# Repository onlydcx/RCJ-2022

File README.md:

# このプロジェクトについて
ロボカップジュニア2022に出場する機体の全データです。要はオープンソースです。

需要があるかは分かりませんが、公開すること自体が大事だと思うので公開します

# 3Dデータ
3Dデータ フォルダに入ってます。

Autodesk Fusion360で作成しました、f3zファイルなのでFusionでしか開けないと思います。

# ソフトウェア
PlatfomIOで開発しています。

必要なplatformio.iniとmain.cppだけ載せておきます。

質問とかあったらTwitterでDMしてください

# 基板データ
基板データ フォルダに入ってます。
- 「CamBoard」 メイン基板のデータです。OpenMV,Teensyなどが乗ります
- 「FrontLine」 前のLINEセンサーのデータです。ボール補足エリアがあるので前だけラインセンサの形が違います。
- 「Kicker」 キッカー用のMOSFETが乗った回路です。コンデンサは別付けです。
- 「PowerUnit」 リポから5V,3.3Vを生成してメイン基板に送る回路です。ヒューズも乗ります。
- 「SideLine」 横と後ろのラインセンサーのデータです
- 「UI-unit」 UI基盤のデータです。0.96inchのOLEDが乗ります

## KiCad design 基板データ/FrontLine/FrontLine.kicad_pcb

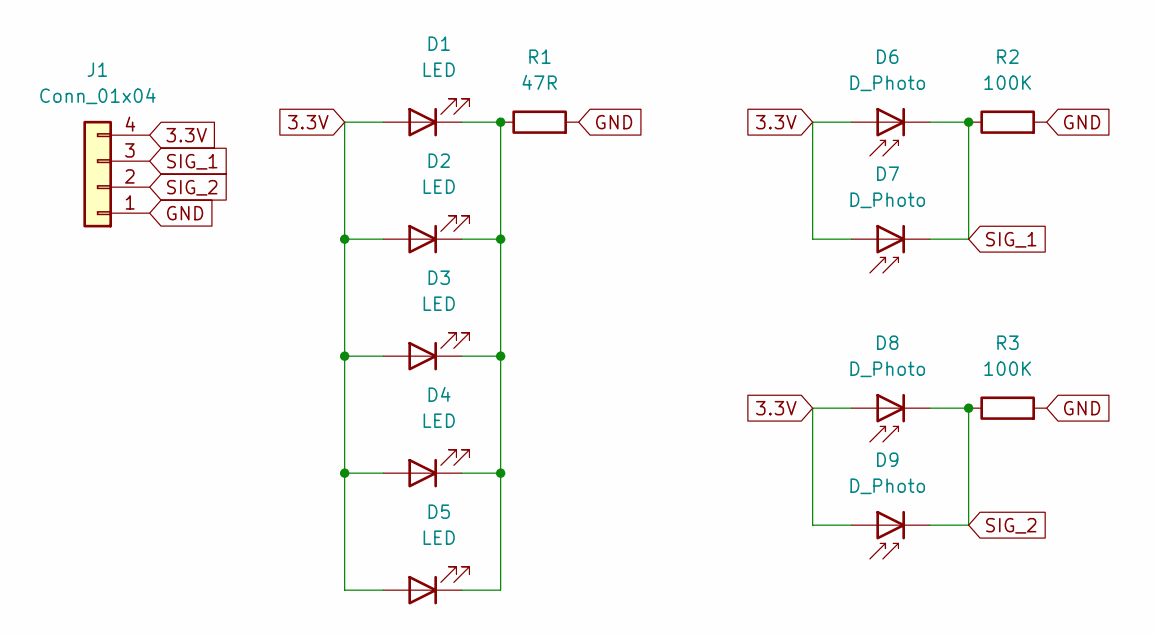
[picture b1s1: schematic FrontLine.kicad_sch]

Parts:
D1, D2, D3, D4, D5: LED; LED_D3.0mm
D6, D7, D8, D9: D_Photo; NJL7302L_F3
J1: Conn_01x04; JST_XH_S4B-XH-A-1_1x04_P2.50mm_Horizontal
R1: 47R; R_Axial_DIN0309_L9.0mm_D3.2mm_P15.24mm_Horizontal
R2, R3: 100K; R_Axial_DIN0309_L9.0mm_D3.2mm_P15.24mm_Horizontal

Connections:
3.3V: D1.2 (A), D2.2 (A), D3.2 (A), D4.2 (A), D5.2 (A), D6.2 (A), D7.2 (A), D8.2 (A), D9.2 (A), J1.4
GND: J1.1, R1.2, R2.2, R3.2
unnamed: D1.1 (K), D2.1 (K), D3.1 (K), D4.1 (K), D5.1 (K), R1.1
SIG_1: D6.1 (K), D7.1 (K), J1.3, R2.1
SIG_2: D8.1 (K), D9.1 (K), J1.2, R3.1

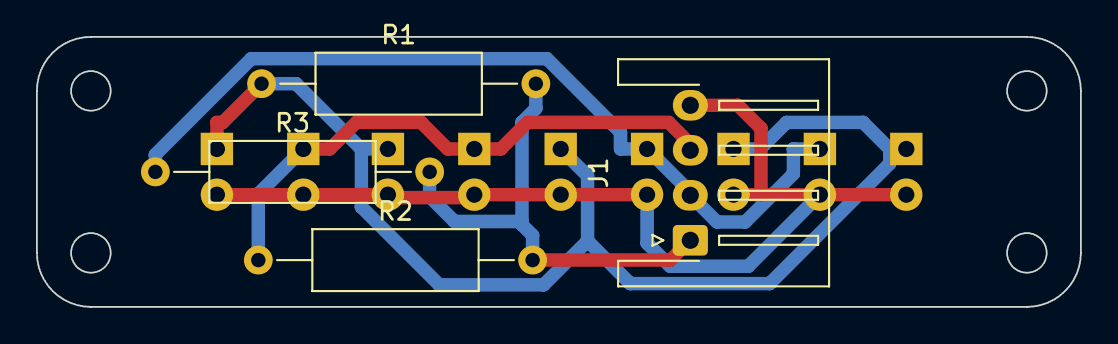
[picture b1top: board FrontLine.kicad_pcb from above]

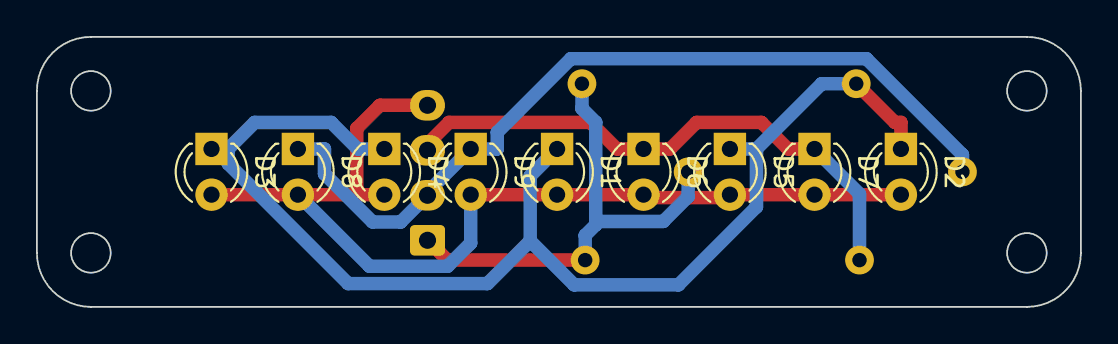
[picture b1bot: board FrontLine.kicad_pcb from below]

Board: 2 copper layers, 58.0 x 15.0 mm, 13 parts (9 on the bottom side), 5 nets.

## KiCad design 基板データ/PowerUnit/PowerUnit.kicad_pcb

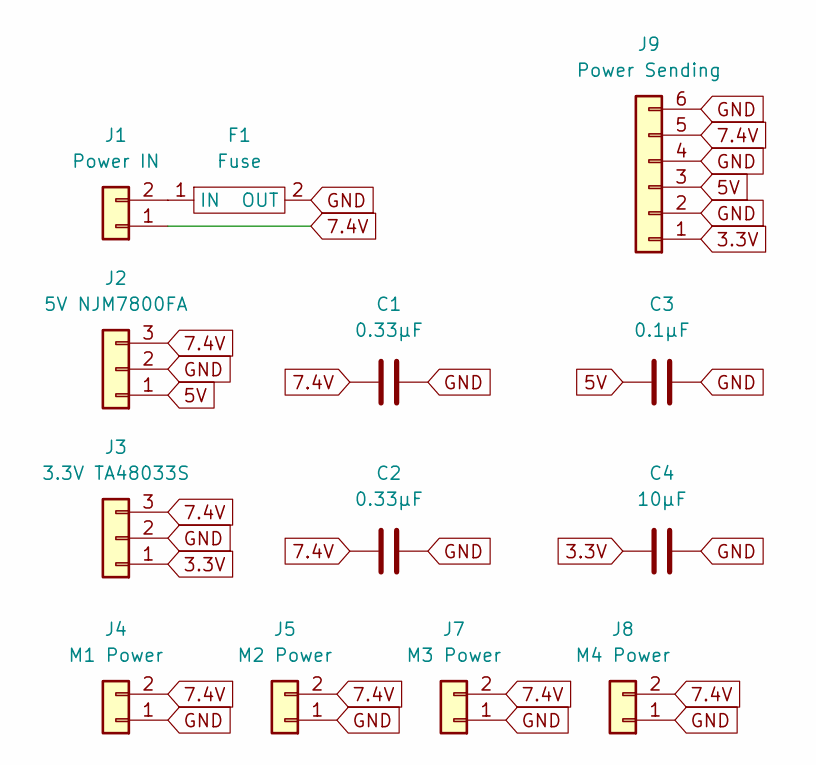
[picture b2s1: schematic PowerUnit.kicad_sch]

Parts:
C1: 0.33μF; PinSocket_1x02_P2.54mm_Vertical
C2: 0.33µF; PinSocket_1x02_P2.54mm_Vertical
C3: 0.1μF; PinSocket_1x02_P2.54mm_Vertical
C4: 10µF; PinSocket_1x02_P2.54mm_Vertical
F1: Fuse
J1: Power IN; JST_VH_S2P-VH_1x02_P3.96mm_Horizontal
J2: 5V NJM7800FA; PinSocket_1x03_P2.54mm_Horizontal
J3: 3.3V TA48033S; PinSocket_1x03_P2.54mm_Horizontal
J4: M1 Power; JST_VH_S2P-VH_1x02_P3.96mm_Horizontal
J5: M2 Power; JST_VH_S2P-VH_1x02_P3.96mm_Horizontal
J7: M3 Power; JST_VH_S2P-VH_1x02_P3.96mm_Horizontal
J8: M4 Power; JST_VH_S2P-VH_1x02_P3.96mm_Horizontal
J9: Power Sending; JST_XH_S6B-XH-A-1_1x06_P2.50mm_Horizontal

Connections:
3.3V: C4.2, J3.1, J9.1
5V: C3.2, J2.1, J9.3
7.4V: C1.2, C2.2, J1.1, J2.3, J3.3, J4.2, J5.2, J7.2, J8.2, J9.5
GND: C1.1, C2.1, C3.1, C4.1, F1.2 (OUT), J2.2, J3.2, J4.1, J5.1, J7.1, J8.1, J9.2, J9.4, J9.6
unnamed: F1.1 (IN), J1.2

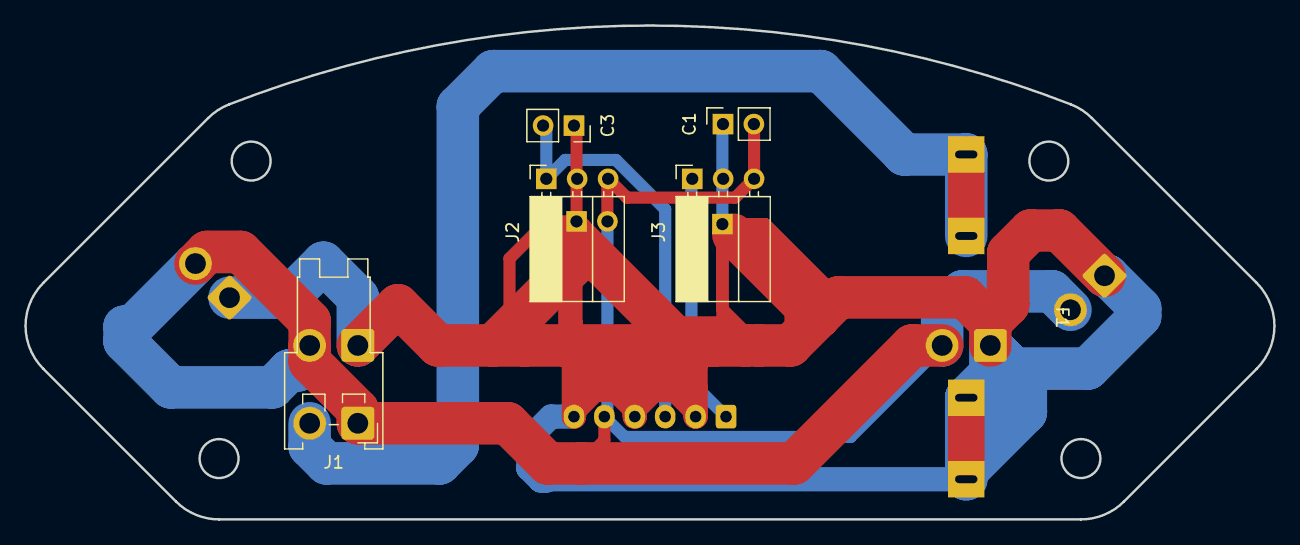
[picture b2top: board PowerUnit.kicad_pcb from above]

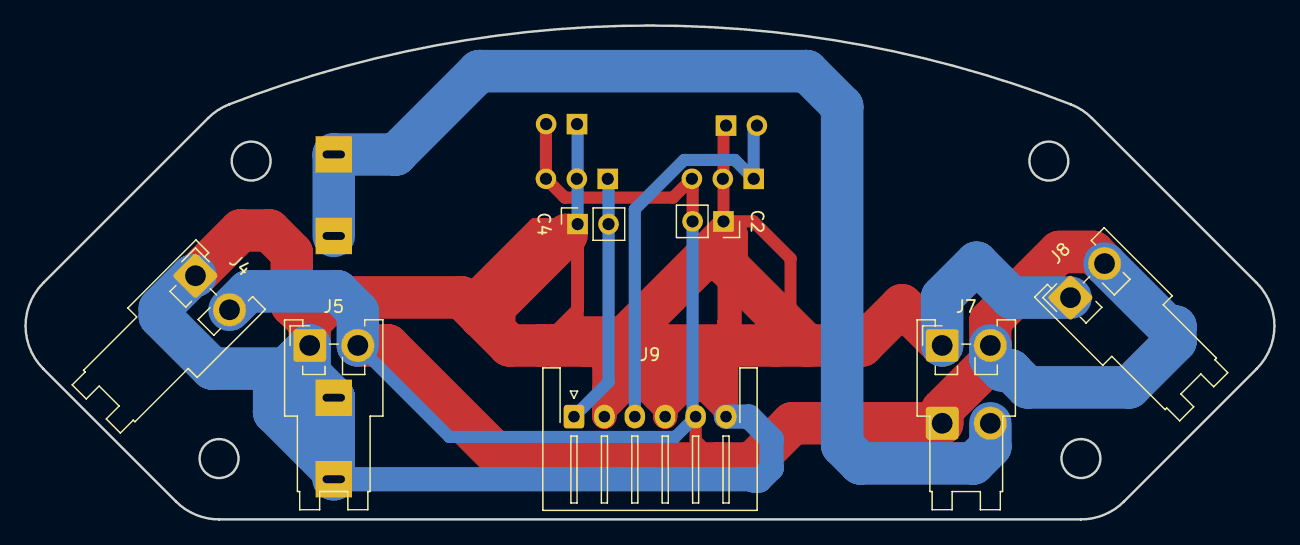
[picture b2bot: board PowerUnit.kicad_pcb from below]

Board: 2 copper layers, 102.7 x 40.6 mm, 13 parts (7 on the bottom side), 5 nets.

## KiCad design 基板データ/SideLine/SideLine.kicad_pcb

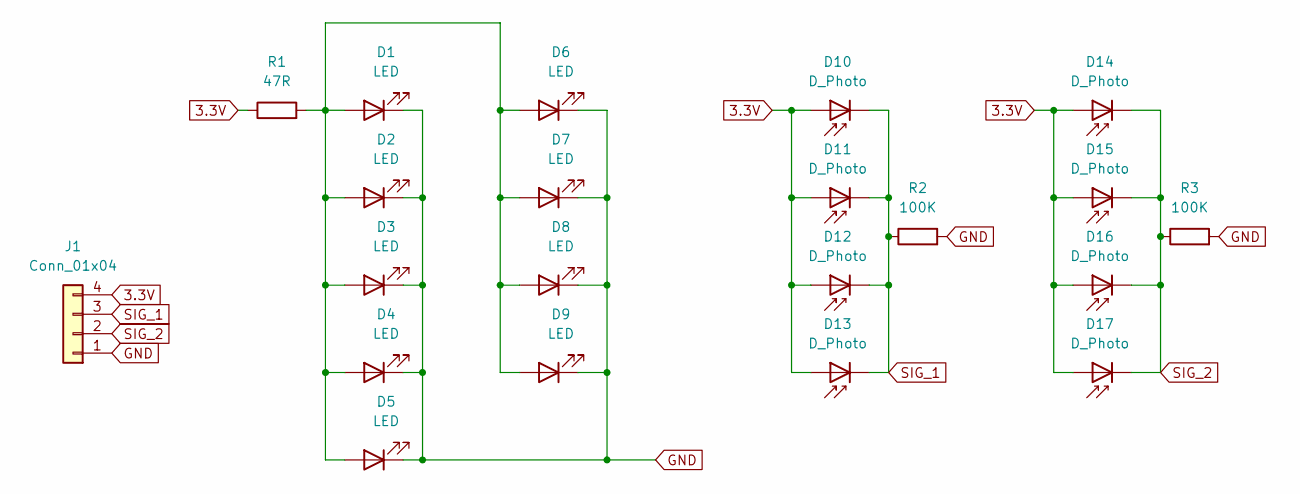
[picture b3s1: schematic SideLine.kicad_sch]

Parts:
D1, D2, D3, D4, D5, D6, D7, D8, D9: LED; LED_D3.0mm
D10, D11, D12, D13, D14, D15, D16, D17: D_Photo; NJL7302L_F3
J1: Conn_01x04; JST_XH_S4B-XH-A-1_1x04_P2.50mm_Horizontal
R1: 47R; R_Axial_DIN0411_L9.9mm_D3.6mm_P15.24mm_Horizontal
R2, R3: 100K; R_Axial_DIN0411_L9.9mm_D3.6mm_P15.24mm_Horizontal

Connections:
3.3V: D10.2 (A), D11.2 (A), D12.2 (A), D13.2 (A), D14.2 (A), D15.2 (A), D16.2 (A), D17.2 (A), J1.4, R1.1
GND: D1.1 (K), D2.1 (K), D3.1 (K), D4.1 (K), D5.1 (K), D6.1 (K), D7.1 (K), D8.1 (K), D9.1 (K), J1.1, R2.2, R3.2
unnamed: D1.2 (A), D2.2 (A), D3.2 (A), D4.2 (A), D5.2 (A), D6.2 (A), D7.2 (A), D8.2 (A), D9.2 (A), R1.2
SIG_1: D10.1 (K), D11.1 (K), D12.1 (K), D13.1 (K), J1.3, R2.1
SIG_2: D14.1 (K), D15.1 (K), D16.1 (K), D17.1 (K), J1.2, R3.1

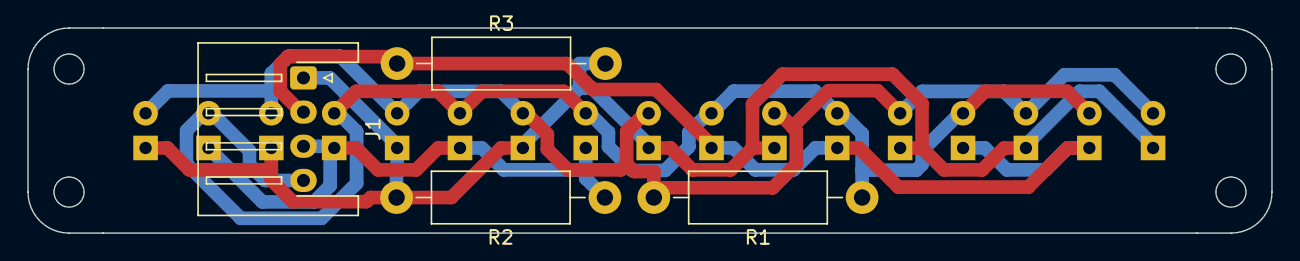
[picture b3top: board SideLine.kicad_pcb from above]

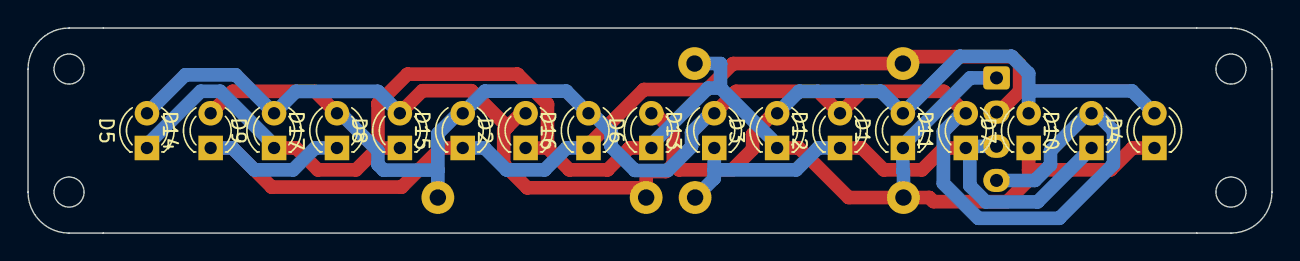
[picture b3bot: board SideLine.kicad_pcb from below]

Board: 2 copper layers, 91.0 x 15.0 mm, 21 parts (17 on the bottom side), 5 nets.

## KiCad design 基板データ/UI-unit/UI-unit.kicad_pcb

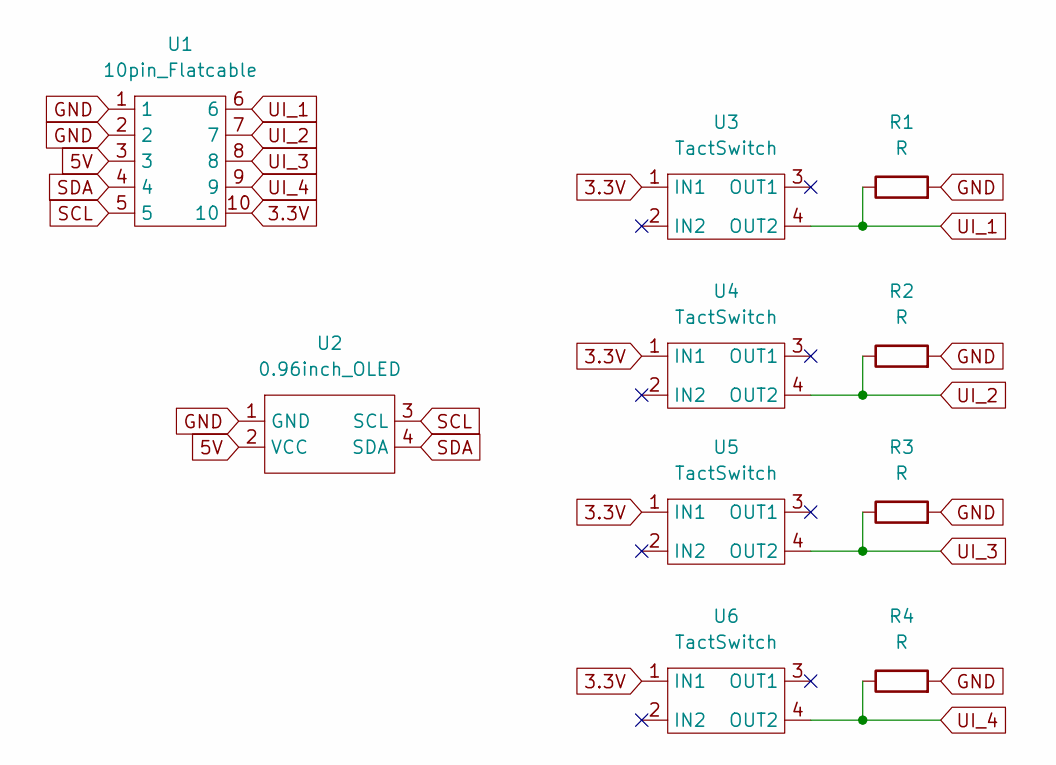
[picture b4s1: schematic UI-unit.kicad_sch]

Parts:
R1, R2, R3, R4: R; R_Axial_DIN0309_L9.0mm_D3.2mm_P12.70mm_Horizontal
U1: 10pin_Flatcable
U2: 0.96inch_OLED
U3, U4, U5, U6: TactSwitch

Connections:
3.3V: U1.10, U3.1 (IN1), U4.1 (IN1), U5.1 (IN1), U6.1 (IN1)
5V: U1.3, U2.2 (VCC)
GND: R1.2, R2.2, R3.2, R4.2, U1.1, U1.2, U2.1 (GND)
SCL: U1.5, U2.3 (SCL)
SDA: U1.4, U2.4 (SDA)
UI_1: R1.1, U1.6, U3.4 (OUT2)
UI_2: R2.1, U1.7, U4.4 (OUT2)
UI_3: R3.1, U1.8, U5.4 (OUT2)
UI_4: R4.1, U1.9, U6.4 (OUT2)

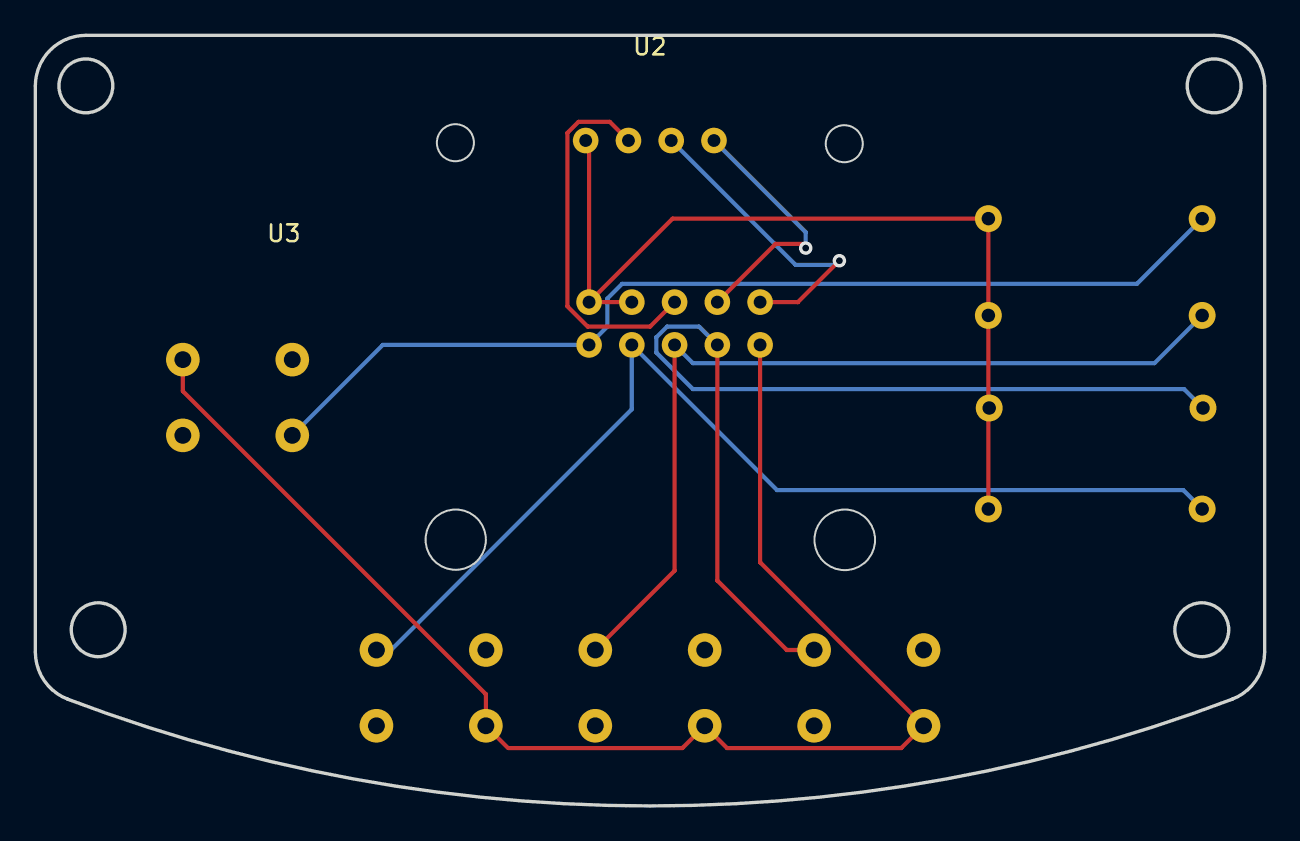
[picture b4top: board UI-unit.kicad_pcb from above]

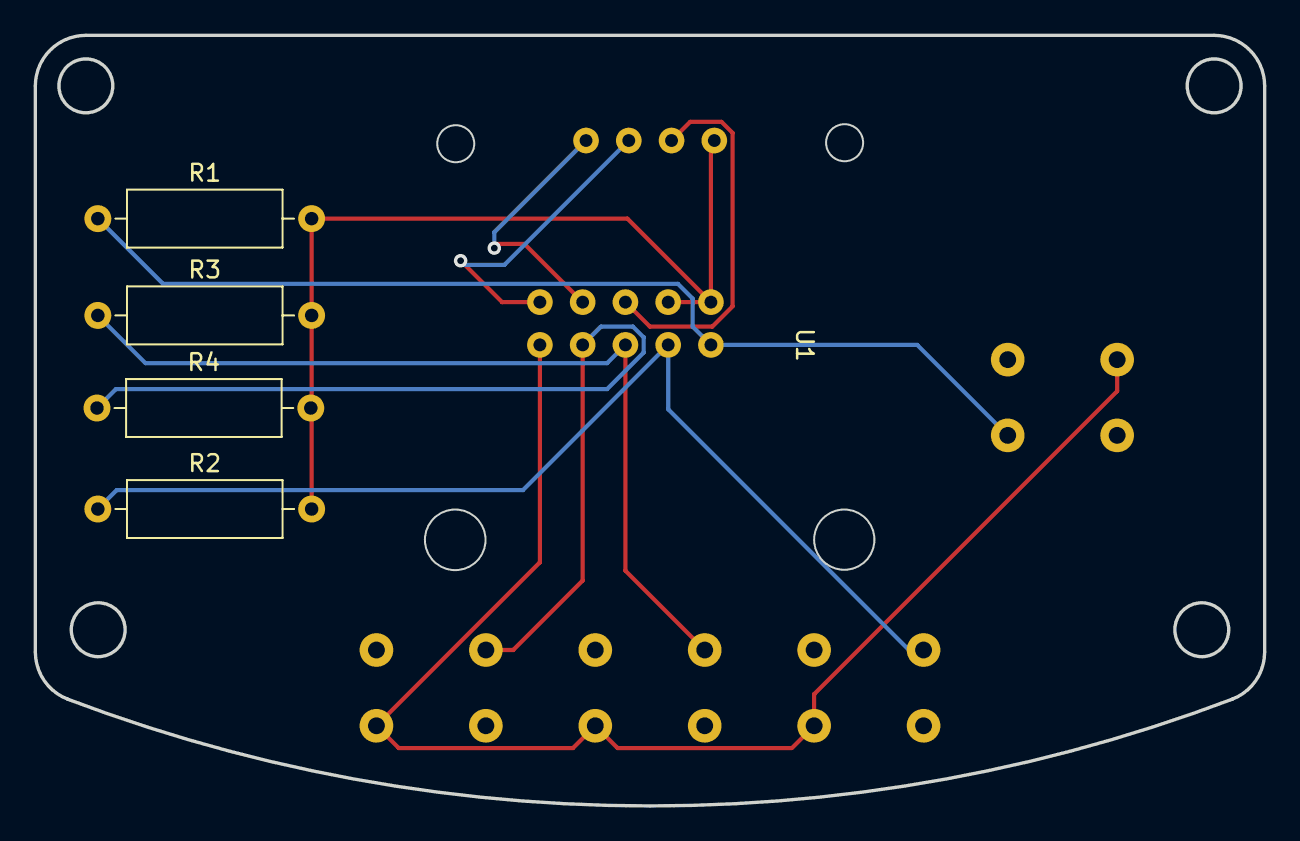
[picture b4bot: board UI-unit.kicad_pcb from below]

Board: 2 copper layers, 73.0 x 45.8 mm, 10 parts (5 on the bottom side), 9 nets.

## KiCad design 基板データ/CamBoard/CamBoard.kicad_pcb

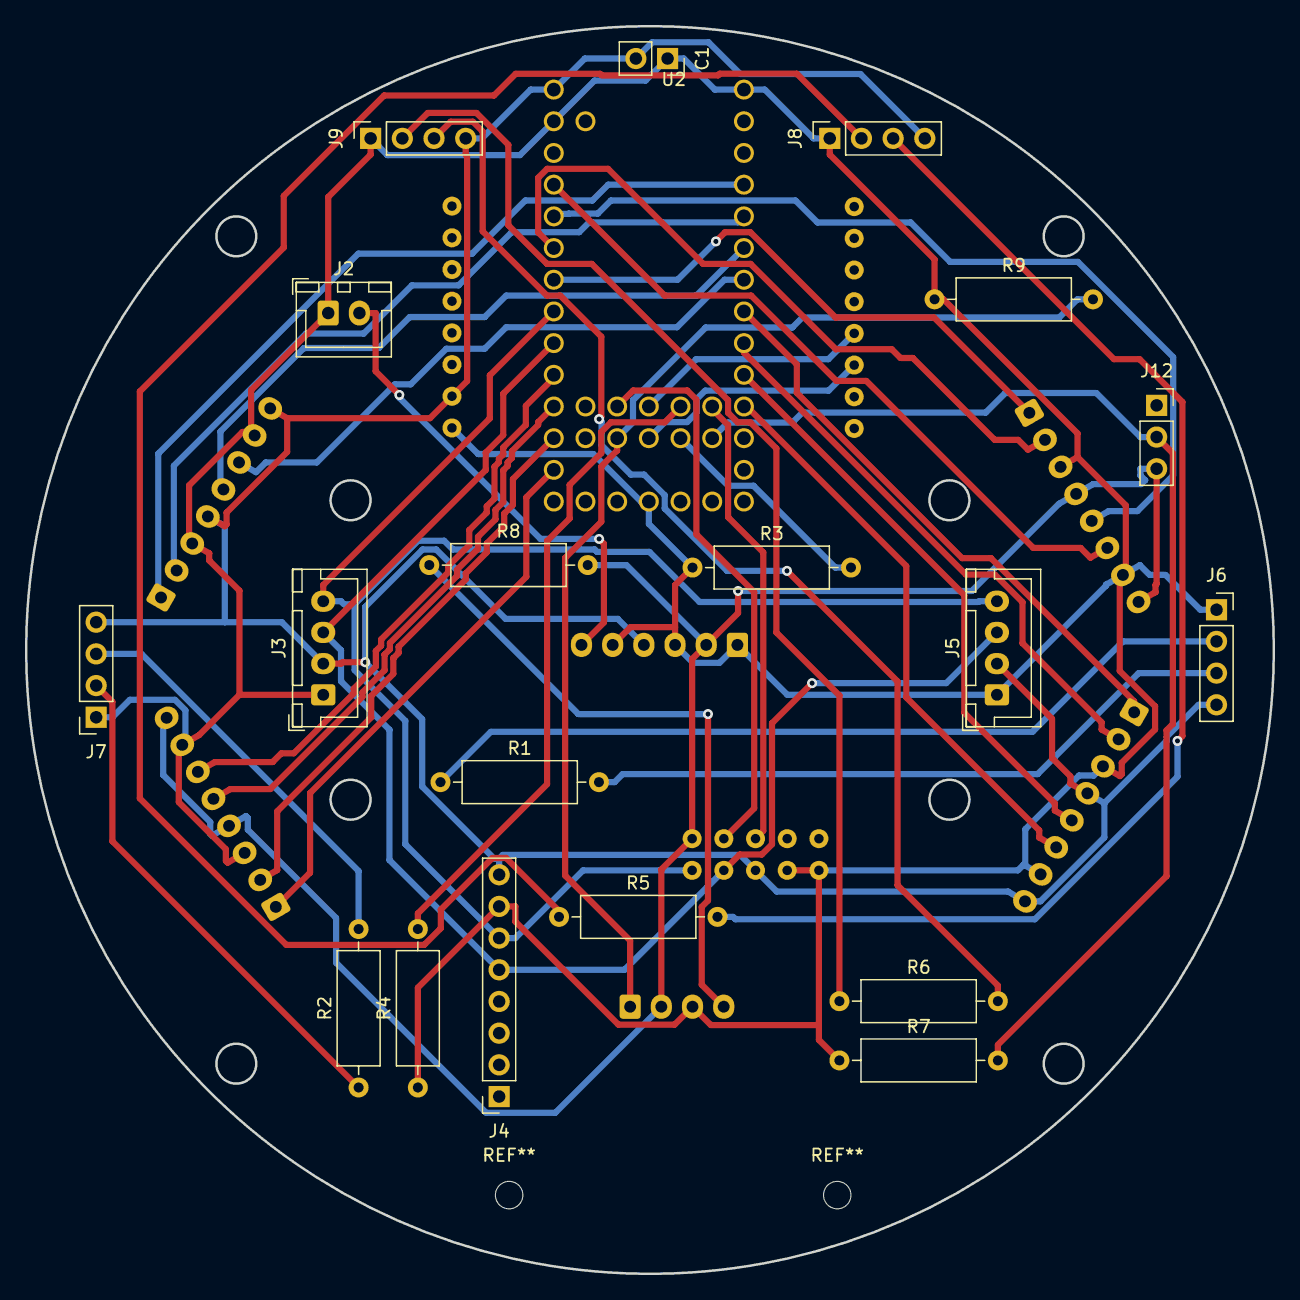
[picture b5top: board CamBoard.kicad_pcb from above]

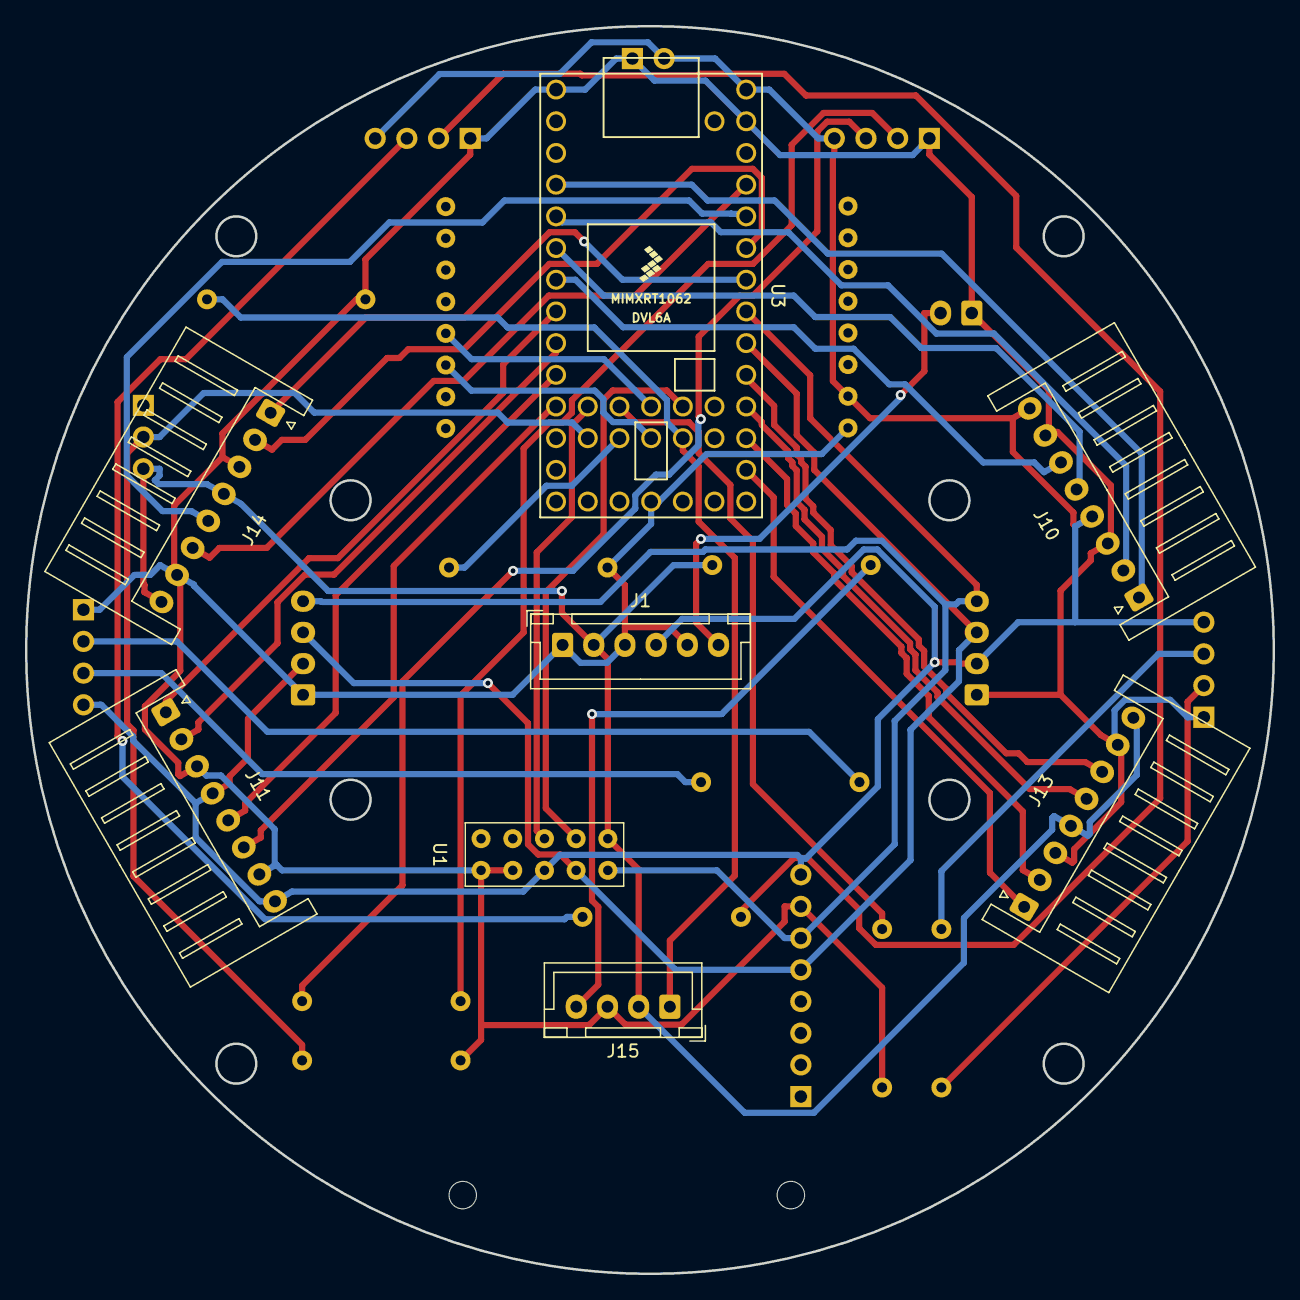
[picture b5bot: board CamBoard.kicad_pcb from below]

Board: 2 copper layers, 100.0 x 100.0 mm, 28 parts (8 on the bottom side), 39 nets.

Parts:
C1: C; PinSocket_1x02_P2.54mm_Vertical
J1: Power IN; JST_XH_B6B-XH-A_1x06_P2.50mm_Vertical
J2: Voltage; JST_XH_B2B-XH-A_1x02_P2.50mm_Vertical
J3, J5: I2C Port; JST_XH_B4B-XH-A_1x04_P2.50mm_Vertical
J4: Gyro; PinSocket_1x08_P2.54mm_Vertical
J6, J7, J8, J9: HC SR04; PinSocket_1x04_P2.54mm_Vertical
J10: Motor Right; JST_XH_S8B-XH-A_1x08_P2.50mm_Horizontal
J11: Motor Left; JST_XH_S8B-XH-A_1x08_P2.50mm_Horizontal
J12: MotorSwitch; PinSocket_1x03_P2.54mm_Vertical
J13: LIne Right; JST_XH_S8B-XH-A_1x08_P2.50mm_Horizontal
J14: Line Left; JST_XH_S8B-XH-A_1x08_P2.50mm_Horizontal
J15: Conn_01x04; JST_XH_B4B-XH-A_1x04_P2.50mm_Vertical
R1, R2, R5, R6: R; R_Axial_DIN0309_L9.0mm_D3.2mm_P12.70mm_Horizontal
R3, R4: 100K; R_Axial_DIN0309_L9.0mm_D3.2mm_P12.70mm_Horizontal
R7, R9: 100k; R_Axial_DIN0309_L9.0mm_D3.2mm_P12.70mm_Horizontal
R8: 47; R_Axial_DIN0309_L9.0mm_D3.2mm_P12.70mm_Horizontal
U1: 10pin_FlatCable; 20pin_FlatCable
U2: OpenMV; OPENMV_H7
U3: Teensy4.0; Teensy40

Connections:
3.3V: J1.2, J12.3, J13.4, J13.8, J14.4, J14.8, J15.2, R8.2, U1.10
5V: C1.2, J1.4, J3.2, J4.8, J5.2, J6.4, J7.4, J8.4, J9.4, J10.4, J10.8, J11.4, J11.8, U1.3, U2.10, U3.33
7.4V: J1.6, J2.2
A0: J13.1, U3.21
A1: J13.2, U3.22
A2: J13.5, U3.23
A3: J13.6, U3.24
A6: J14.1, U3.27
A7: J14.2, U3.28
A8: J14.5, U3.29
A9: J14.6, U3.30
A12: J15.1, R9.2, U3.37
GND: C1.1, J1.1, J1.3, J1.5, J2.1, J3.1, J4.7, J5.1, J6.1, J7.1, J8.1, J9.1, J10.3, J10.7, J11.3, J11.7, J13.3, J13.7, J14.3, J14.7, J15.3, R3.1, R4.1, R7.1, R9.1, U1.1, U1.2, U2.9, U3.1, U3.17, U3.32
HC-SR04-Back: J8.3, R5.2
HC-SR04-Front: J6.3, R1.2
HC-SR04-Left: J7.3, R2.2
HC-SR04-Right: J9.3, R6.2
LED1: R4.2, U3.42
LED2: R3.2, U3.41
M1_DIR: J10.2, U3.5
M1_PWM: J10.1, U3.4
M2_DIR: J10.6, U3.7
M2_PWM: J10.5, U3.6
M3_DIR: J11.2, U3.9
M3_PWM: J11.1, U3.8
M4_DIR: J11.6, U3.11
M4_PWM: J11.5, U3.10
unnamed: J6.2, R1.1
unnamed: J7.2, R2.1
unnamed: J8.2, R5.1
unnamed: J9.2, R6.1
unnamed: J12.2, R7.2, U3.43
unnamed: J15.4, R8.1
RX: U2.3, U3.39
SCL: J3.4, J4.6, J5.4, U1.5, U3.26
SDA: J3.3, J4.5, J5.3, U1.4, U3.25
TX: U2.4, U3.40
UI_3: U1.8, U3.44
UI_4: U1.9, U3.38

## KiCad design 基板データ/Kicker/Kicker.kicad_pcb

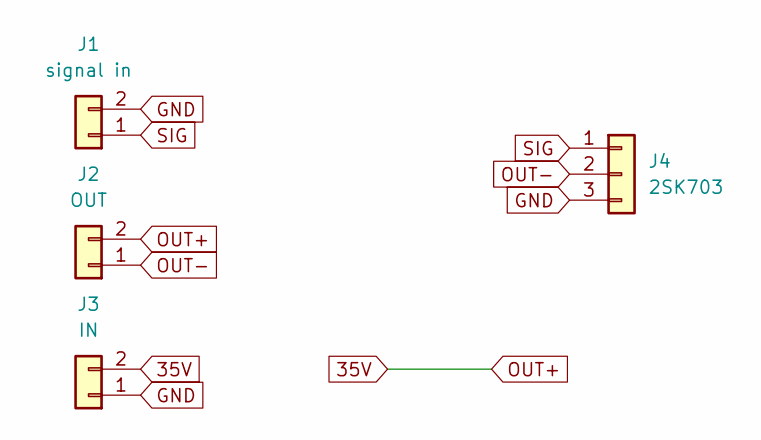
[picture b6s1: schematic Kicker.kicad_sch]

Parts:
J1: signal in; JST_XH_S2B-XH-A_1x02_P2.50mm_Horizontal
J2: OUT; JST_VH_B2PS-VH_1x02_P3.96mm_Horizontal
J3: IN; JST_VH_B2PS-VH_1x02_P3.96mm_Horizontal
J4: 2SK703; PinSocket_1x03_P2.54mm_Vertical

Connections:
35V: J2.2, J3.2
GND: J1.2, J3.1, J4.3
OUT-: J2.1, J4.2
SIG: J1.1, J4.1

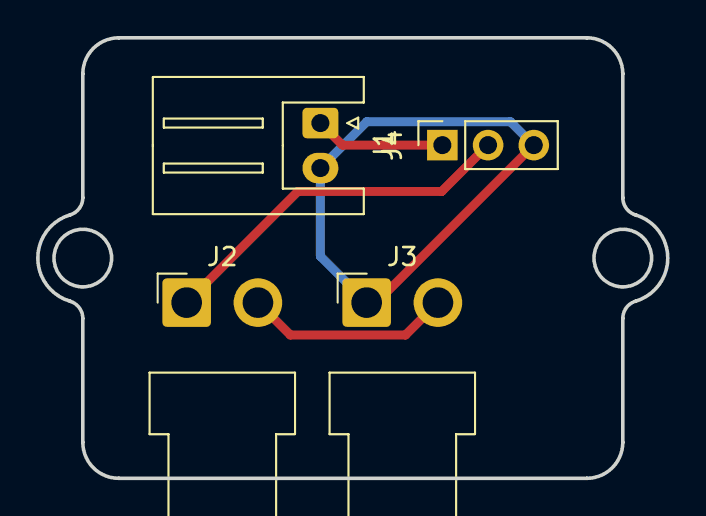
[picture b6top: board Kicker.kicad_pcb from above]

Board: 2 copper layers, 35.0 x 24.5 mm, 4 parts (0 on the bottom side), 4 nets.

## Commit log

2022-03-30 基板データを更新
2022-03-30 3Dデータを追加
2022-03-30 ソースコードを追加
2022-03-30 説明を追加
2022-04-08 ラインセンサの動きを調整 & キッカー関数を改良(未動作)
    ラインセンサ・・・白線検出時、一定時間白線方向に向かわないように改良
    キッカー・・・他の動作に影響が出ないようにmillsを使って書き直し(動作未確認)
    モーター・・・動きながら常に0度を向くように調整
2022-04-08 OpenMV.pyを作成
